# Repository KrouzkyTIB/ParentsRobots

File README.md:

# ParentsRobots
Repozitář s kódem a hardwarovými schématy pro kroužek bastelní s rodiči.

##### Jak zvolit jméno WiFi sítě robota?
 Na robotovi je 3-bitový mikro přepínač, kde pomocí navolením 0 a 1 zvolíme jméno WiFi sítě. Volíme v binární soustavě, takže je možné navolit až 8 jmen.
 
 ##### Jak se připojit k robotovi?
 Robot vytvoří svou vlastní wifi síť, ke které se můžete připojit pomocí Vašeho telefonu. Uživatelé s telefony s operačním systémem Android 10 a výš mohou
 mít problém s tím, že telefon hlásí, že v síti nedetekuje připojení k internetu. Zde pomáhá nastavit telefon pro tuto síť na statickou ip adresu.
 Ip adresa: 192.168.1.50
 Brána/Gateway: 192.168.1.1
 DNS 1: 0.0.0.0
 DNS 2: 0.0.0.0
 
 ##### Jak ovládat robota?
 Otevřete si prohlížeč na Vašem telefonu a do url boxíku napište IP adresu robota 192.168.1.10. Poté se Vám v telefonu objeví stránka na ovládání robota. 
 Na stránce naleznete joystick pro jízdu a tlačítko pro zapnutí světel.

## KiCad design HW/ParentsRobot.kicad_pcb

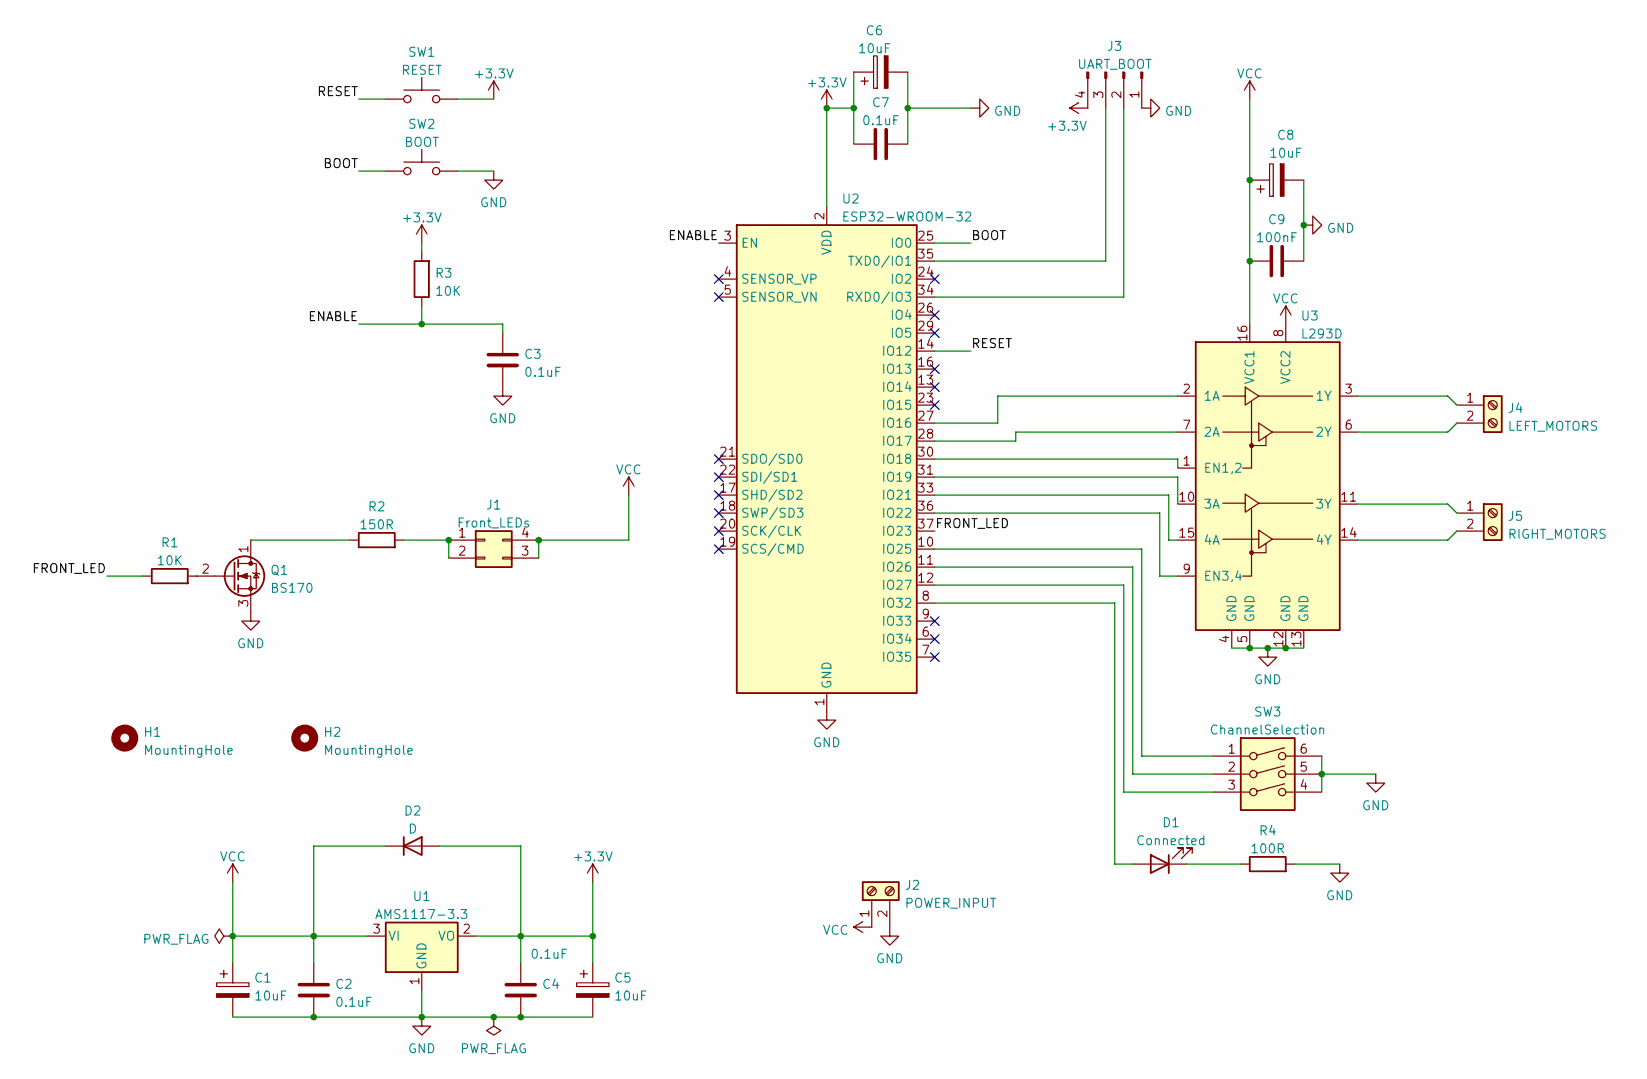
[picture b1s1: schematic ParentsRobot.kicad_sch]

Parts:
C1, C5, C6, C8: 10uF; CP_Radial_D4.0mm_P1.50mm
C2, C3, C4, C7: 0.1uF; C_Disc_D5.0mm_W2.5mm_P5.00mm
C9: 100nF; C_Disc_D5.0mm_W2.5mm_P5.00mm
D1: Connected; LED_D3.0mm_Clear
D2: D; D_DO-41_SOD81_P7.62mm_Horizontal
H1, H2: MountingHole; MountingHole_3.2mm_M3
J1: Front_LEDs; PinHeader_2x02_P2.54mm_Vertical
J2: POWER_INPUT; TerminalBlock_Altech_AK300-2_P5.00mm
J3: UART_BOOT; PinHeader_1x04_P2.54mm_Vertical
J4: LEFT_MOTORS; TerminalBlock_Altech_AK300-2_P5.00mm
J5: RIGHT_MOTORS; TerminalBlock_Altech_AK300-2_P5.00mm
Q1: BS170; TO-92_Inline
R1, R3: 10K; R_Axial_DIN0207_L6.3mm_D2.5mm_P7.62mm_Horizontal
R2: 150R; R_Axial_DIN0207_L6.3mm_D2.5mm_P7.62mm_Horizontal
R4: 100R; R_Axial_DIN0207_L6.3mm_D2.5mm_P7.62mm_Horizontal
SW1: RESET; SW_PUSH_6mm
SW2: BOOT; SW_PUSH_6mm
SW3: ChannelSelection; SW_DIP_SPSTx03_Slide_9.78x9.8mm_W7.62mm_P2.54mm
U1: AMS1117-3.3; SOT-223-3_TabPin2
U2: ESP32-WROOM-32
U3: L293D; DIP-16_W7.62mm

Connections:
+3V3: C4.1, C5.1, C6.1, C7.1, D2.2 (A), J3.4, R3.2, SW1.2, U1.2 (VO), U2.2 (VDD)
/BOOT: SW2.1, U2.25 (IO0)
/ENABLE: C3.1, R3.1, U2.3 (EN)
/FRONT_LED: R1.1, U2.37 (IO23)
/RESET: SW1.1, U2.14 (IO12)
GND: C1.2, C2.2, C3.2, C4.2, C5.2, C6.2, C7.2, C8.2, C9.2, J2.2, J3.1, Q1.3 (S), R4.2, SW2.2, SW3.4, SW3.5, SW3.6, U1.1 (GND), U2.1 (GND), U2.15 (GND), U2.38 (GND), U2.39 (GND), U3.4 (GND), U3.5 (GND), U3.12 (GND), U3.13 (GND)
unnamed: D1.1 (K), R4.1
unnamed: D1.2 (A), U2.8 (IO32)
unnamed: J3.2, U2.34 (RXD0/IO3)
unnamed: J3.3, U2.35 (TXD0/IO1)
unnamed: J4.1, U3.3 (1Y)
unnamed: J4.2, U3.6 (2Y)
unnamed: J5.1, U3.11 (3Y)
unnamed: J5.2, U3.14 (4Y)
unnamed: Q1.1 (D), R2.1
unnamed: Q1.2 (G), R1.2
unnamed: J1.1, J1.2, R2.2
unnamed: SW3.1, U2.10 (IO25)
unnamed: SW3.2, U2.11 (IO26)
unnamed: SW3.3, U2.12 (IO27)
unnamed: U2.27 (IO16), U3.2 (1A)
unnamed: U2.28 (IO17), U3.7 (2A)
unnamed: U2.30 (IO18), U3.1 (EN1,2)
unnamed: U2.31 (IO19), U3.10 (3A)
unnamed: U2.33 (IO21), U3.15 (4A)
unnamed: U2.36 (IO22), U3.9 (EN3,4)
VCC: C1.1, C2.1, C8.1, C9.1, D2.1 (K), J1.3, J1.4, J2.1, U1.3 (VI), U3.8 (VCC2), U3.16 (VCC1)

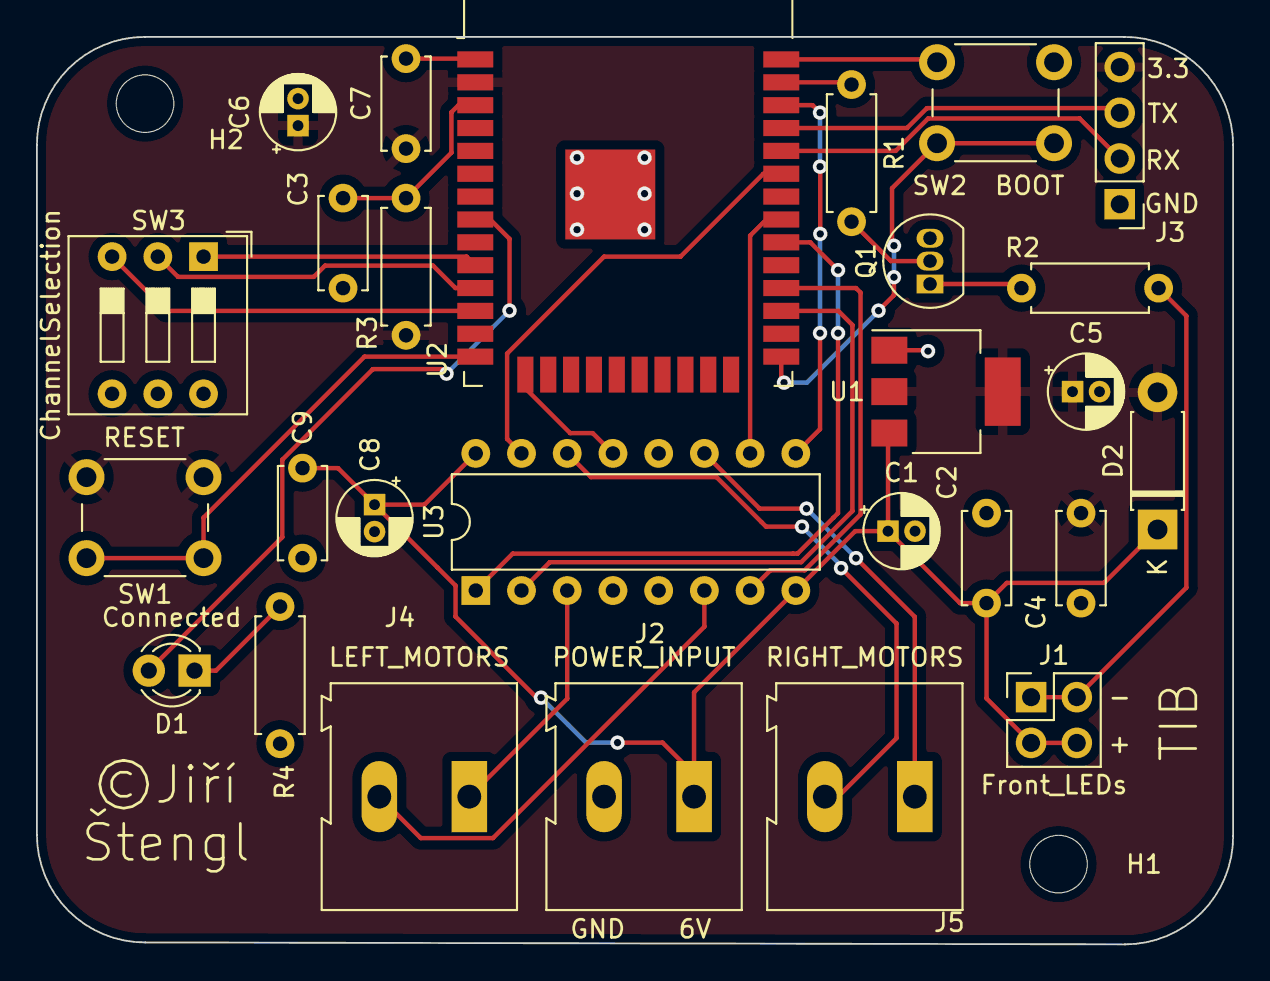
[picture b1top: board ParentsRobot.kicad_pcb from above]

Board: 2 copper layers, 66.5 x 50.4 mm, 29 parts (0 on the bottom side), 27 nets.

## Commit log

2022-06-25 Done schematic
2022-06-25 Done schematic. Repaired wrong used buttons and connector for front leds + assigned footprints
2022-06-25 Almost done PCB. Drill holes needs to be added
2022-06-25 Hardware done
2022-06-25 Added output directory for gerbers to gitingore
2022-06-25 Final version to manufacturer
2022-07-31 created driver for motors
2022-07-31 Created FE react app + sliders
2022-08-05 Working FE joystick
2022-08-05 Prepared button for turn on/off lights
2022-08-05 styled button for turning on/off lights
2022-08-07 Prepared data sending for robot. Also prepared data models
2022-08-29 Prepared front end for sending data to backend
2022-08-29 Done FE
2022-09-10 done webpack configuration and build of application
2022-09-10 front end build + webpack config
2022-09-10 prepared wifi and http server for communiaction
2022-09-10 prepared deploy
2022-09-10 prepared server for body parse
2022-09-11 fixed server but problem with page size
2022-09-11 Working serving of page to the user + gzipped page
2022-09-11 beutified code
2022-09-11 fixed front end to send data
2022-09-11 working communication between front end and backend
2022-09-11 Done joystick math
2022-09-11 working code for parsing json from front end
2022-09-11 working parsing and propagating data from front end
2022-09-11 redone front end communication
2022-09-12 done wifi channel reading
2022-09-12 added wifi led signal, when setup ready
2023-01-12 Fixed minor issues
2023-01-12 Added front LED controller
2023-01-12 Prepared code for lesson

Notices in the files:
HW/ParentsRobot.kicad_pcb:
©Jiří
